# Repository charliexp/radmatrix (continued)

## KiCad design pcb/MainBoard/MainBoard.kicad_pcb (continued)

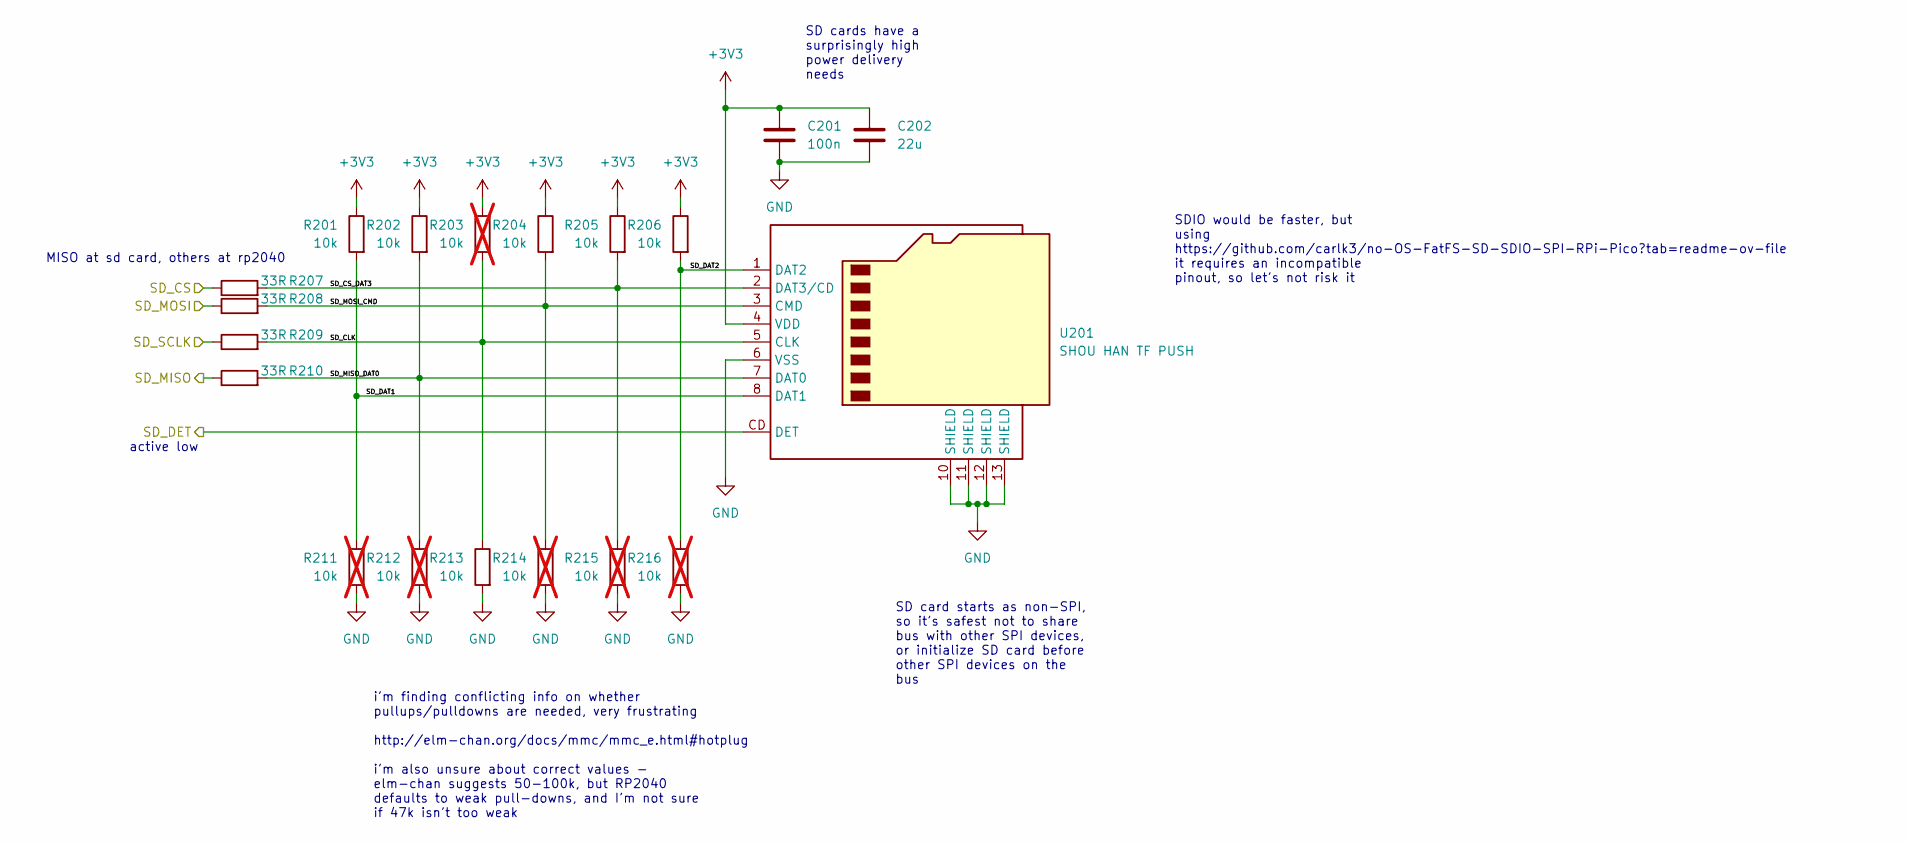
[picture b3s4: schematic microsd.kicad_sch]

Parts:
C201: 100n; C_0402_1005Metric; LCSC C1525
C202: 22u; C_0805_2012Metric; LCSC C45783
R201, R202, R204, R205, R206, R213: 10k; R_0603_1608Metric; LCSC C25804
R203, R211, R212, R214, R215, R216: 10k; R_0603_1608Metric; LCSC C25804; not fitted
R207, R208, R209, R210: 33R; R_0402_1005Metric; LCSC C25105
U201: SHOU HAN TF PUSH; micro-sd-tf-push; LCSC C393941

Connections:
+3V3: C201.1, C202.1, R201.1, R202.1, R203.1, R204.1, R205.1, R206.1, U201.4 (VDD); also elsewhere on the board
/SD_CS: R207.1; also elsewhere on the board
/SD_DET: U201.CD (DET); also elsewhere on the board
/SD_MISO: R210.1; also elsewhere on the board
/SD_MOSI: R208.1; also elsewhere on the board
/SD_SCLK: R209.1; also elsewhere on the board
/microsd/SD_CLK: R203.2, R209.2, R213.1, U201.5 (CLK)
/microsd/SD_CS_DAT3: R205.2, R207.2, R215.1, U201.2 (DAT3/CD)
/microsd/SD_DAT1: R201.2, R211.1, U201.8 (DAT1)
/microsd/SD_DAT2: R206.2, R216.1, U201.1 (DAT2)
/microsd/SD_MISO_DAT0: R202.2, R210.2, R212.1, U201.7 (DAT0)
/microsd/SD_MOSI_CMD: R204.2, R208.2, R214.1, U201.3 (CMD)
GND: C201.2, C202.2, R211.2, R212.2, R213.2, R214.2, R215.2, R216.2, U201.6 (VSS), U201.10 (SHIELD), U201.11 (SHIELD), U201.12 (SHIELD), U201.13 (SHIELD); also elsewhere on the board

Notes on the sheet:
SD card starts as non-SPI, so it's safest not to share bus with other SPI devices, or initialize SD card before other SPI devices on the bus
i'm finding conflicting info on whether pullups/pulldowns are needed, very frustrating http://elm-chan.org/docs/mmc/mmc_e.html#hotplug i'm also unsure about correct values - elm-chan suggests 50-100k, but RP2040 defaults to weak pull-downs, and I'm not sure if 47k isn't too weak
SD cards have a surprisingly high power delivery needs
SDIO would be faster, but using https://github.com/carlk3/no-OS-FatFS-SD-SDIO-SPI-RPi-Pico?tab=readme-ov-file it requires an incompatible pinout, so let's not risk it
active low
MISO at sd card, others at rp2040

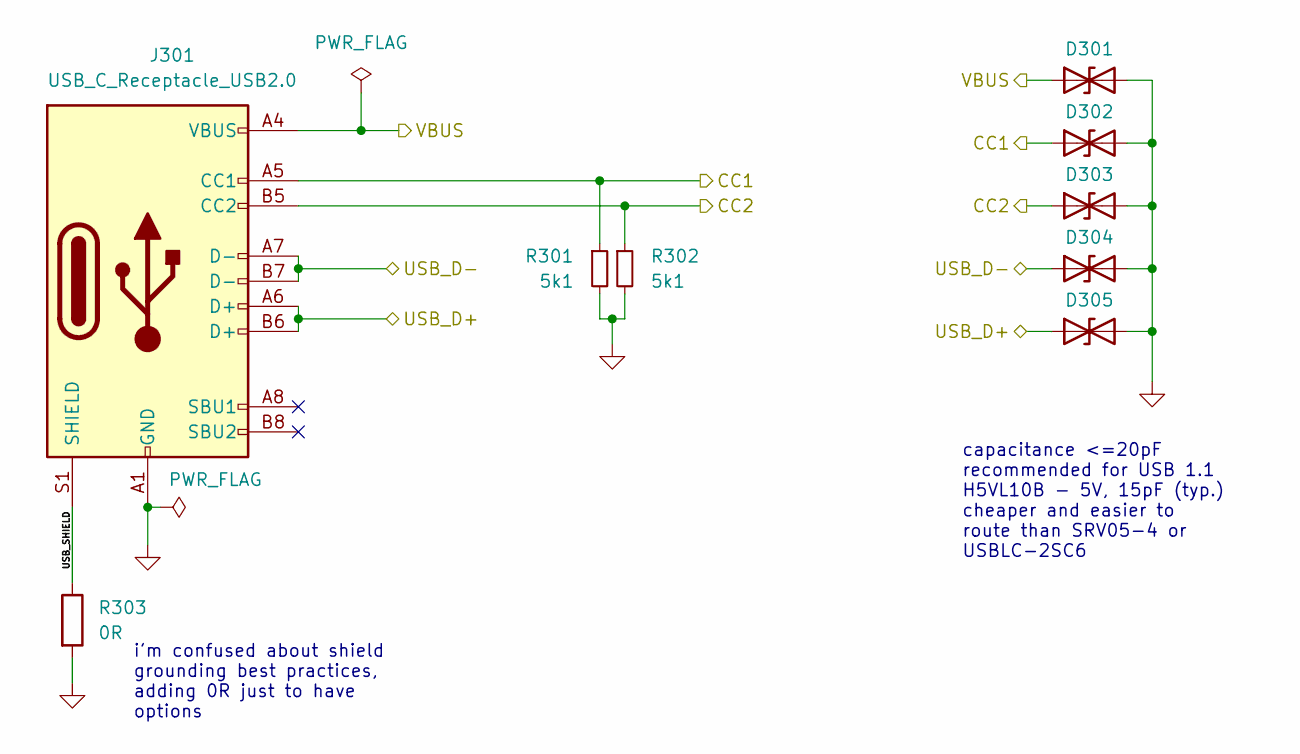
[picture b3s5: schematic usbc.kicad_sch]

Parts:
D301, D302, D303, D304, D305: H5VL10B; DFN1006_TVS; LCSC C7420372
J301: USB_C_Receptacle_USB2.0; USB_C_Receptacle_HRO_TYPE-C-31-M-12; LCSC C165948
R301, R302: 5k1; R_0402_1005Metric; LCSC C25905
R303: 0R; R_0603_1608Metric; LCSC C21189

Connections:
/CC1: D302.1 (A1), J301.A5 (CC1), R301.1; also elsewhere on the board
/CC2: D303.1 (A1), J301.B5 (CC2), R302.1; also elsewhere on the board
/USB_D+: D305.1 (A1), J301.A6 (D+), J301.B6 (D+); also elsewhere on the board
/USB_D-: D304.1 (A1), J301.A7 (D-), J301.B7 (D-); also elsewhere on the board
/power/VBUS: D301.1 (A1), J301.A4 (VBUS), J301.A9 (VBUS), J301.B4 (VBUS), J301.B9 (VBUS); also elsewhere on the board
/usbc/USB_SHIELD: J301.S1 (SHIELD), R303.1
GND: D301.2 (A2), D302.2 (A2), D303.2 (A2), D304.2 (A2), D305.2 (A2), J301.A1 (GND), J301.A12 (GND), J301.B1 (GND), J301.B12 (GND), R301.2, R302.2, R303.2; also elsewhere on the board

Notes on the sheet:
capacitance <=20pF recommended for USB 1.1 H5VL10B - 5V, 15pF (typ.) cheaper and easier to route than SRV05-4 or USBLC-2SC6
i'm confused about shield grounding best practices, adding 0R just to have options

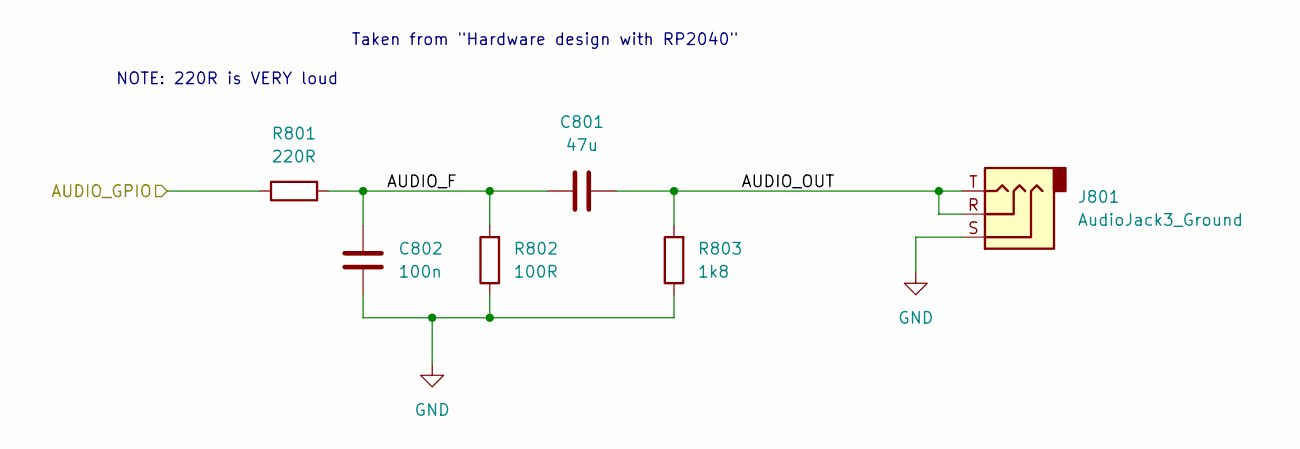
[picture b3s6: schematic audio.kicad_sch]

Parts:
C801: 47u; C_0805_2012Metric; LCSC C16780
C802: 100n; C_0402_1005Metric; LCSC C1525
J801: AudioJack3_Ground; 3.5mm-audio-jack
R801: 220R; R_0603_1608Metric; LCSC C22962
R802: 100R; R_0402_1005Metric; LCSC C25076
R803: 1k8; R_0603_1608Metric; LCSC C4177

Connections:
/AUDIO_GPIO: R801.1; also elsewhere on the board
/audio/AUDIO_F: C801.1, C802.1, R801.2, R802.2
/audio/AUDIO_OUT: C801.2, J801.R, J801.T, R803.2
GND: C802.2, J801.S, R802.1, R803.1; also elsewhere on the board

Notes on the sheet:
NOTE: 220R is VERY loud
Taken from "Hardware design with RP2040"

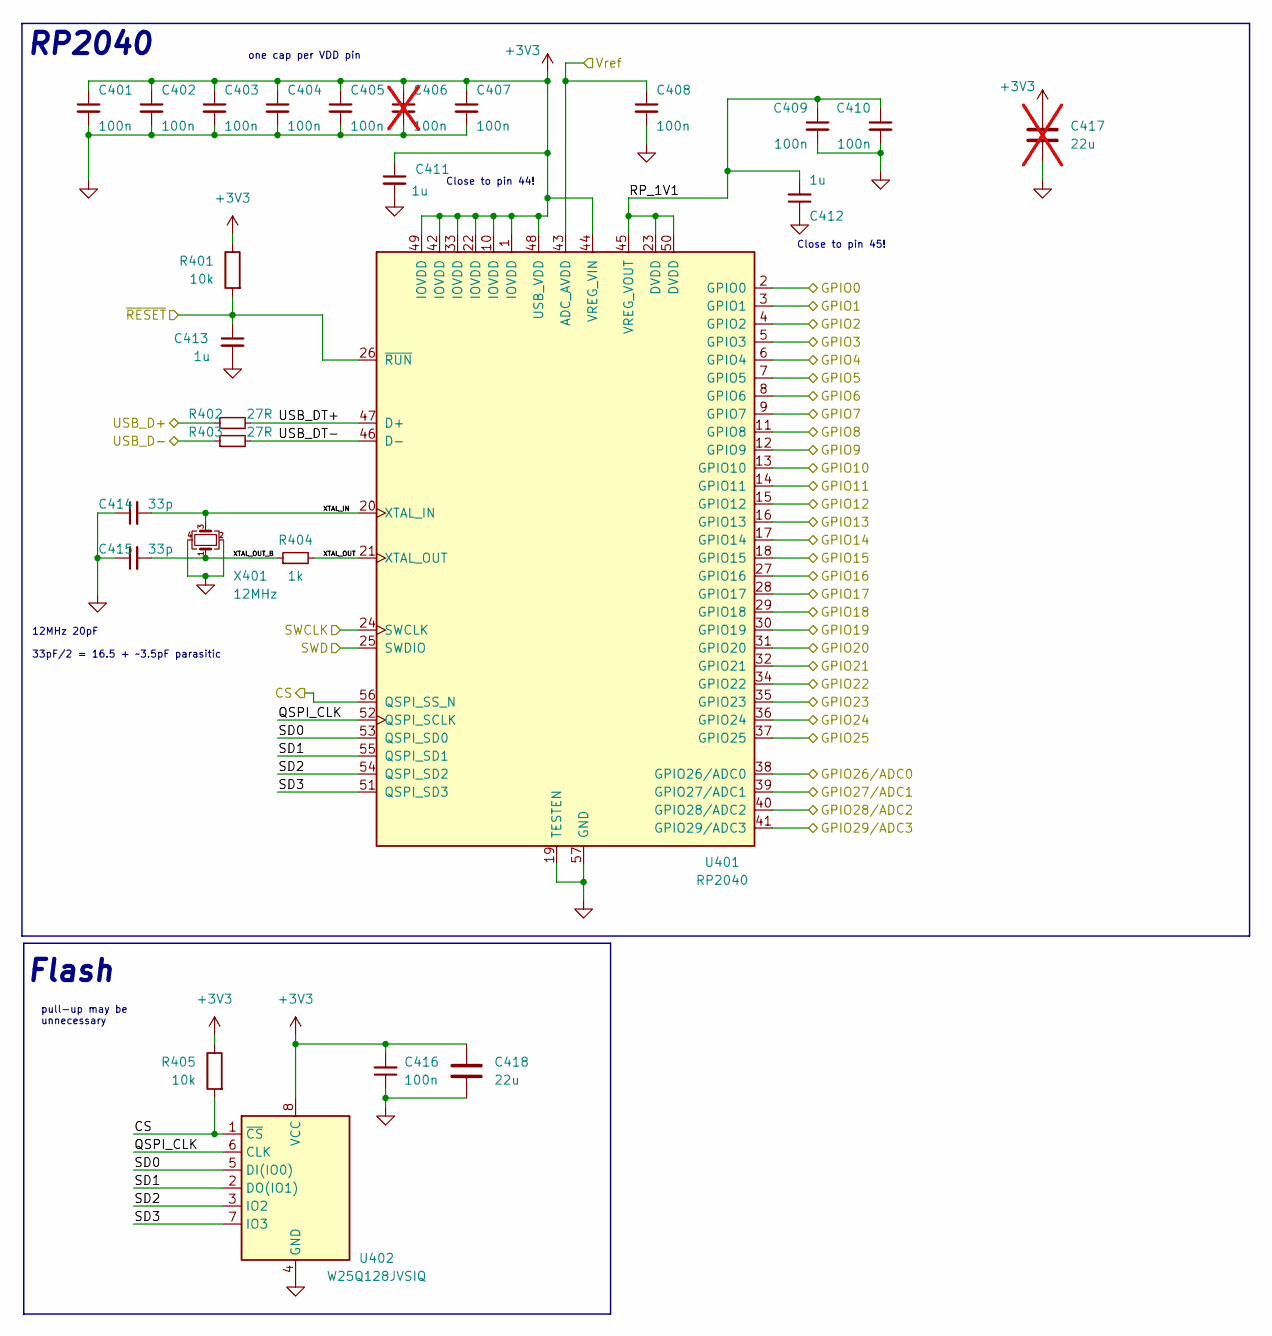
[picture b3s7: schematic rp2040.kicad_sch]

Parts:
C401, C402, C403, C404, C405, C407, C408, C409, C410, C416: 100n; C_0402_1005Metric; LCSC C1525
C406: 100n; C_0402_1005Metric; LCSC C1525; not fitted
C411, C412, C413: 1u; C_0402_1005Metric; LCSC C52923
C414, C415: 33p; C_0402_1005Metric; LCSC C1570
C417: 22u; C_0805_2012Metric; LCSC C45783; not fitted
C418: 22u; C_0805_2012Metric; LCSC C45783
R401, R405: 10k; R_0402_1005Metric; LCSC C25744
R402, R403: 27R; R_0603_1608Metric; LCSC C25190
R404: 1k; R_0402_1005Metric; LCSC C11702
U401: RP2040; RP2040-QFN-56; LCSC C2040
U402: W25Q128JVSIQ; SOIC-8_5.23x5.23mm_P1.27mm; LCSC C97521
X401: 12MHz; Crystal_SMD_3225-4Pin_3.2x2.5mm; LCSC C9002

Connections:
+3V3: C401.1, C402.1, C403.1, C404.1, C405.1, C406.1, C407.1, C411.1, C416.2, C417.1, C418.1, R401.1, R405.1, U401.1 (IOVDD), U401.10 (IOVDD), U401.22 (IOVDD), U401.33 (IOVDD), U401.42 (IOVDD), U401.44 (VREG_VIN), U401.48 (USB_VDD), U401.49 (IOVDD), U402.8 (VCC); also elsewhere on the board
/5v_sense_F: U401.40 (GPIO28/ADC2); also elsewhere on the board
/AUDIO_GPIO: U401.11 (GPIO8); also elsewhere on the board
/CAN_RXD: U401.7 (GPIO5); also elsewhere on the board
/CAN_S: U401.8 (GPIO6); also elsewhere on the board
/CAN_TXD: U401.9 (GPIO7); also elsewhere on the board
/CC1_F: U401.38 (GPIO26/ADC0); also elsewhere on the board
/CC2_F: U401.39 (GPIO27/ADC1); also elsewhere on the board
/COL_RCLK: U401.35 (GPIO23); also elsewhere on the board
/COL_SER: U401.32 (GPIO21); also elsewhere on the board
/COL_SRCLK: U401.36 (GPIO24); also elsewhere on the board
/COL_~OE: U401.34 (GPIO22); also elsewhere on the board
/COL_~SRCLR: U401.37 (GPIO25); also elsewhere on the board
/CS: R405.2, U401.56 (QSPI_SS_N), U402.1 (~CS); also elsewhere on the board
/GPIO9: U401.12 (GPIO9); also elsewhere on the board
/GPIO10: U401.13 (GPIO10); also elsewhere on the board
/GPIO11: U401.14 (GPIO11); also elsewhere on the board
/GPIO12: U401.15 (GPIO12); also elsewhere on the board
/GPIO13: U401.16 (GPIO13); also elsewhere on the board
/Isense_F: U401.41 (GPIO29/ADC3); also elsewhere on the board
/ROW_RCLK: U401.31 (GPIO20); also elsewhere on the board
/ROW_SER_J: U401.17 (GPIO14); also elsewhere on the board
/ROW_SRCLK: U401.29 (GPIO18); also elsewhere on the board
/ROW_~OE: U401.30 (GPIO19); also elsewhere on the board
/ROW_~SRCLR_J: U401.18 (GPIO15); also elsewhere on the board
/SD_CS: U401.3 (GPIO1); also elsewhere on the board
/SD_DET: U401.6 (GPIO4); also elsewhere on the board
/SD_MISO: U401.2 (GPIO0); also elsewhere on the board
/SD_MOSI: U401.5 (GPIO3); also elsewhere on the board
/SD_SCLK: U401.4 (GPIO2); also elsewhere on the board
/SWCLK: U401.24 (SWCLK); also elsewhere on the board
/SWD: U401.25 (SWDIO); also elsewhere on the board
/UART_RX: U401.28 (GPIO17); also elsewhere on the board
/UART_TX: U401.27 (GPIO16); also elsewhere on the board
/USB_D+: R402.1; also elsewhere on the board
/USB_D-: R403.1; also elsewhere on the board
/rp2040/QSPI_CLK: U401.52 (QSPI_SCLK), U402.6 (CLK)
/rp2040/RP_1V1: C409.1, C410.1, C412.2, U401.23 (DVDD), U401.45 (VREG_VOUT), U401.50 (DVDD)
/rp2040/SD0: U401.53 (QSPI_SD0), U402.5 (DI(IO0))
/rp2040/SD1: U401.55 (QSPI_SD1), U402.2 (DO(IO1))
/rp2040/SD2: U401.54 (QSPI_SD2), U402.3 (IO2)
/rp2040/SD3: U401.51 (QSPI_SD3), U402.7 (IO3)
/rp2040/USB_DT+: R402.2, U401.47 (D+)
/rp2040/USB_DT-: R403.2, U401.46 (D-)
/rp2040/XTAL_IN: C414.2, U401.20 (XTAL_IN), X401.3
/rp2040/XTAL_OUT: R404.2, U401.21 (XTAL_OUT)
/rp2040/XTAL_OUT_B: C415.2, R404.1, X401.1
/~RESET: C413.1, R401.2, U401.26 (~RUN); also elsewhere on the board
GND: C401.2, C402.2, C403.2, C404.2, C405.2, C406.2, C407.2, C408.2, C409.2, C410.2, C411.2, C412.1, C413.2, C414.1, C415.1, C416.1, C417.2, C418.2, U401.19 (TESTEN), U401.57 (GND), U402.4 (GND), X401.2, X401.4; also elsewhere on the board
Vref: C408.1, U401.43 (ADC_AVDD); also elsewhere on the board

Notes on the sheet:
pull-up may be unnecessary
Close to pin 45!
one cap per VDD pin
12MHz 20pF 33pF/2 = 16.5 + ~3.5pF parasitic
Close to pin 44!
RP2040
Flash

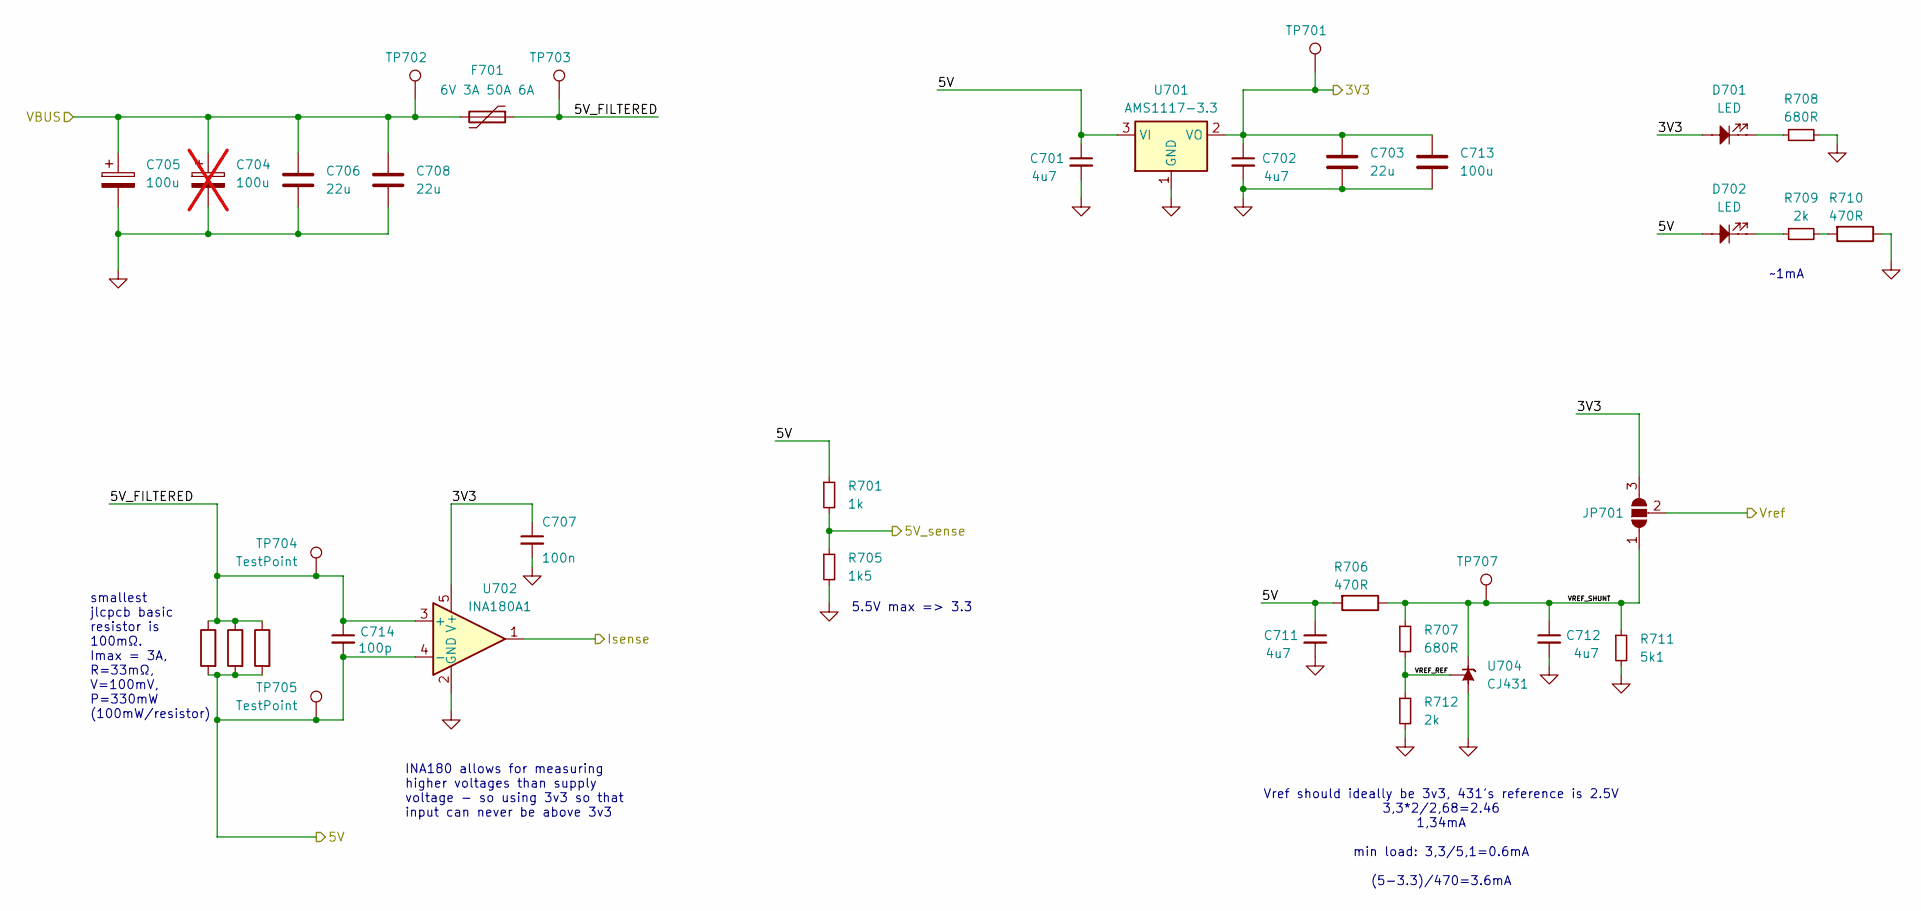
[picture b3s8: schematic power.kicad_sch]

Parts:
C701, C702, C711, C712: 4u7; C_0805_2012Metric; LCSC C1779
C703, C706, C708: 22u; C_0805_2012Metric; LCSC C45783
C704: 100u; CP_EIA-3528-15_AVX-H; LCSC C16133; not fitted
C705: 100u; CP_Elec_6.3x7.7
C707: 100n; C_0402_1005Metric; LCSC C1525
C713: 100u; C_1206_3216Metric; LCSC C15008
C714: 100p; C_0402_1005Metric; LCSC C1546
D701, D702: LED; D_0603_1608Metric; LCSC C2986059
F701: 6V 3A 50A 6A; Fuse_1210_3225Metric_Pad1.42x2.65mm_HandSolder; LCSC C2844234
JP701: SolderJumper_3_Open; SolderJumper-3_Open_RoundedPad_Smol
R701: 1k; R_0402_1005Metric; LCSC C11702
R702, R703, R704: 100mΩ; R_1206_3216Metric; LCSC C25334
R705: 1k5; R_0402_1005Metric; LCSC C25867
R706, R710: 470R; R_0603_1608Metric; LCSC C23179
R707, R708: 680R; R_0402_1005Metric; LCSC C25130
R709, R712: 2k; R_0402_1005Metric; LCSC C4109
R711: 5k1; R_0402_1005Metric; LCSC C25905
TP701, TP702, TP703, TP704, TP705, TP707: TestPoint; TestPoint_Pad_D1.0mm
U701: AMS1117-3.3; SOT-223-3_TabPin2; LCSC C6186
U702: INA180A1; SOT-23-5; LCSC C122228
U704: CJ431; SOT-23; LCSC C3113

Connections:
+3V3: C702.1, C703.1, C707.1, C713.1, D701.2, JP701.3 (B), TP701.1, U701.2 (VO), U702.5 (V+); also elsewhere on the board
+5V: C701.1, C711.1, C714.2, D702.2, R701.1, R702.2, R703.2, R704.2, R706.2, TP705.1, U701.3 (VI), U702.4 (-); also elsewhere on the board
/5V_sense: R701.2, R705.1; also elsewhere on the board
/Isense: U702.1; also elsewhere on the board
/power/5V_FILTERED: C714.1, F701.1, R702.1, R703.1, R704.1, TP703.1, TP704.1, U702.3 (+)
/power/VBUS: C704.1, C705.1, C706.1, C708.1, F701.2, TP702.1; also elsewhere on the board
/power/VREF_REF: R707.2, R712.1, U704.2 (REF)
/power/VREF_SHUNT: C712.1, JP701.1 (A), R706.1, R707.1, R711.1, TP707.1, U704.1 (K)
GND: C701.2, C702.2, C703.2, C704.2, C705.2, C706.2, C707.2, C708.2, C711.2, C712.2, C713.2, R705.2, R708.1, R710.1, R711.2, R712.2, U701.1 (GND), U702.2 (GND), U704.3 (A); also elsewhere on the board
unnamed: D701.1, R708.2
unnamed: D702.1, R709.1
unnamed: R709.2, R710.2
Vref: JP701.2 (C); also elsewhere on the board

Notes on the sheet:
smallest jlcpcb basic resistor is 100mΩ. Imax = 3A, R=33mΩ, V=100mV, P=330mW (100mW/resistor)
INA180 allows for measuring higher voltages than supply voltage - so using 3v3 so that input can never be above 3v3
~1mA
5.5V max => 3.3
Vref should ideally be 3v3, 431's reference is 2.5V 3,3*2/2,68=2.46 1,34mA min load: 3,3/5,1=0.6mA (5-3.3)/470=3.6mA

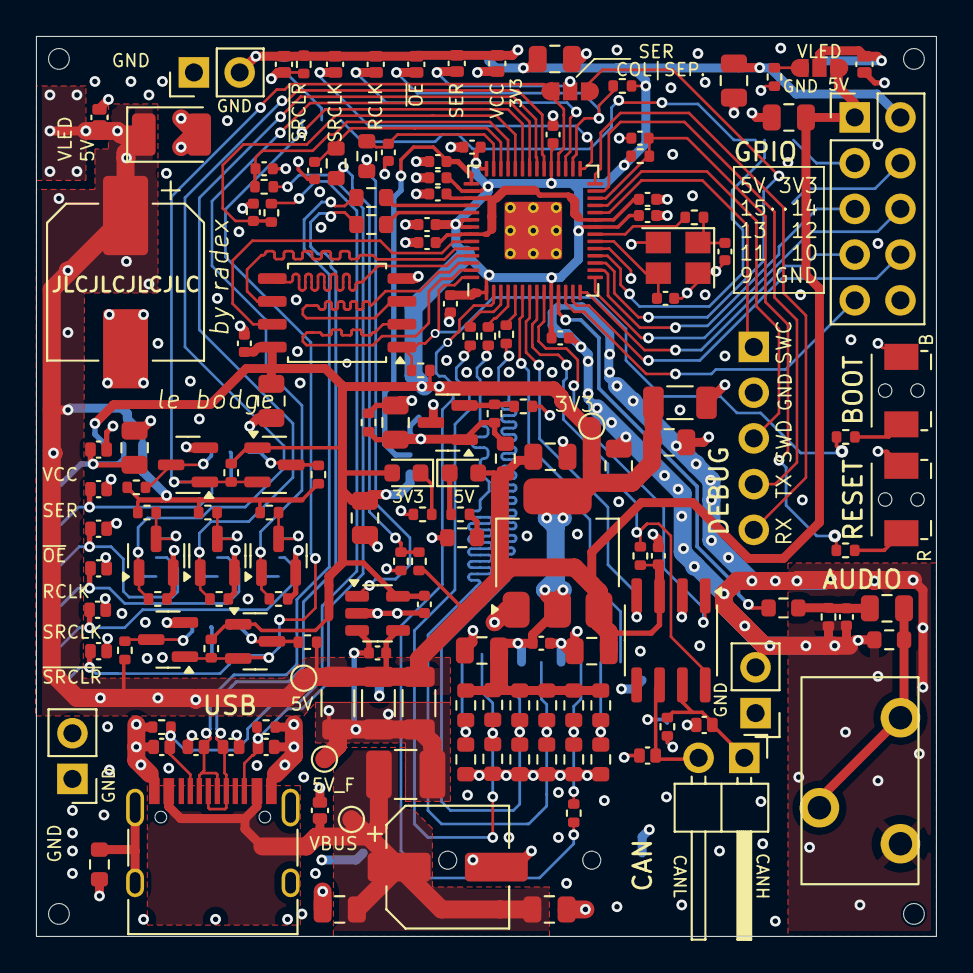
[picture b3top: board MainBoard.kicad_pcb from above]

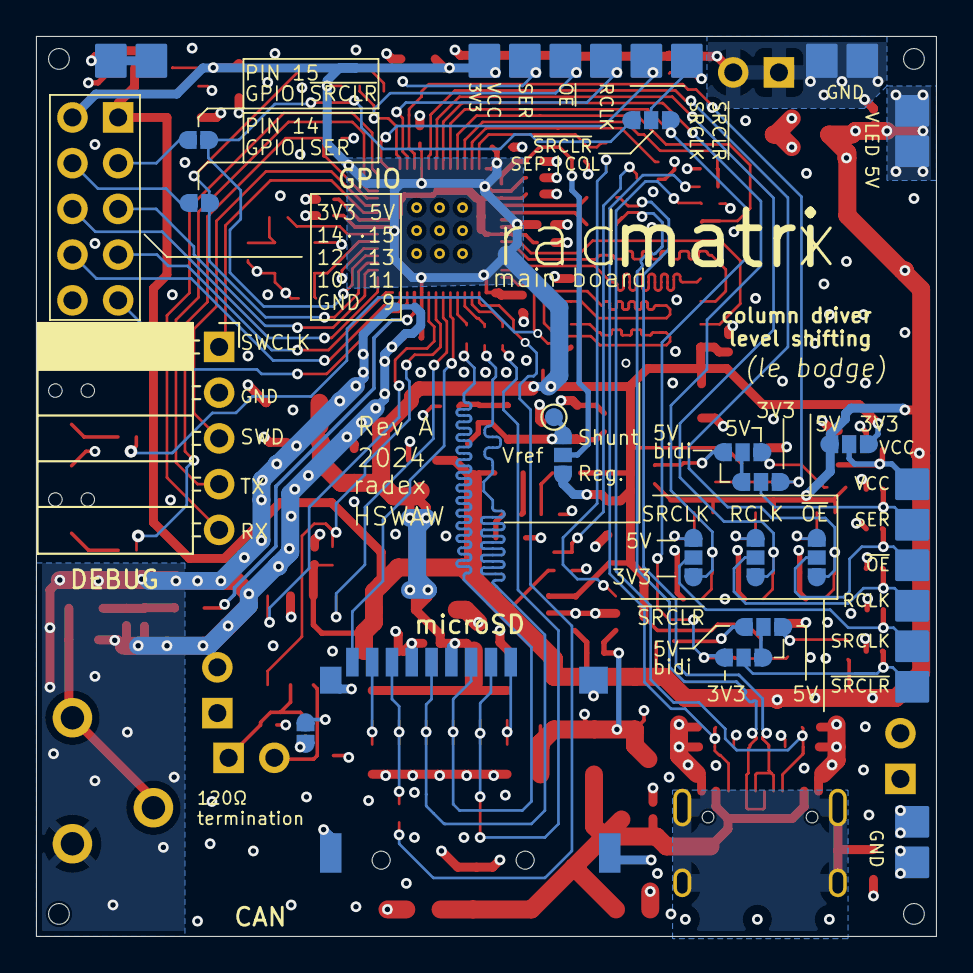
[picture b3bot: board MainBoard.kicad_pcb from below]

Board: 4 copper layers, 50.0 x 50.0 mm, 198 parts (36 on the bottom side), 97 nets.

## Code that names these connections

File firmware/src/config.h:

#pragma once

#ifndef _config_h
#define _config_h

// --- pinout ---

#define AUDIO_PIN 8

#define SD_PIN_SS 1
#define SD_PIN_SCK 2
#define SD_PIN_MOSI 3
#define SD_PIN_MISO 0
#define SD_HAS_DETECTION true
#define SD_DET_PIN 4

#define CAN_ENABLED true
#define CAN_PIN_RX 5
#define CAN_PIN_TX 7
#define CAN_PIN_SILENT 6

#define UART_TX_PIN 16
#define UART_RX_PIN 17

// NOTE: with current layout, 9-15 are free GPIOs (14, 15 only when using shared SER, SRCLR)
#define NEXT_PIN 9

#define CC1_PIN 26
#define CC2_PIN 27
#define V_SENSE_PIN 28
#define I_SENSE_PIN 29

#if CC1_PIN < 26 || CC1_PIN > 29 || \
    CC2_PIN < 26 || CC2_PIN > 29 || \
    V_SENSE_PIN < 26 || V_SENSE_PIN > 29 || \
    I_SENSE_PIN < 26 || I_SENSE_PIN > 29
#error "Invalid ADC pin"
#endif

// --- pinout - screen ---

// #define COMMON_SER 21
// #define COMMON_RCLK 23
// #define COMMON_SRCLR 25

#define COL_SER 21 // orig: 21
#define COL_OE 22 // orig: 22
#define COL_RCLK 23 // orig: 23
#define COL_SRCLK 24 // orig: 24
#define COL_SRCLR 25 // orig: 25

#define ROW_SER 14
#define ROW_OE 19
#define ROW_RCLK 20
#define ROW_SRCLK 18
#define ROW_SRCLR 15

#define COL_SER_INVERTED true
#define COL_OE_INVERTED false
#define COL_RCLK_INVERTED false
#define COL_SRCLK_INVERTED false
#define COL_SRCLR_INVERTED false

// --- screen settings ---

#define ROW_MODULES 3
#define COL_MODULES 4

#define COLOR_BITS 8

#define MAX_FPS 30
#define MAX_LENGTH_MIN 10

#define ROW_COUNT ROW_MODULES * 20
#define COL_COUNT COL_MODULES * 20

// --- audio settings ---

#define AUDIO_RATE 44000.0f
#define BUFFER_LEN 512*16

// --- other settings ---

#define CPU_CLOCK_HZ 133000000.0f
#define SD_CARD_BAUD_RATE 12 * 1000 * 1000
#define REFERENCE_VOLTAGE 3.3f // for ADC
#define CURRENT_FACTOR 1.0f // for current sensor
#define CAN_BITRATE 500000

// --- debug settings ---

#define DEBUG_TEST_FRAME false
#define DEBUG_FIRST_FRAME false
#define DEBUG_FRAMEBUFFER false

// --- screen - performance ---
// NOTE: In case of screen glitching, these may need to be tweaked to decrease
// data rate to the display and stay within the limits of the hardware/electrical connection
#define LEDS_PIO_CLKDIV 3
// Also see leds.pio where delays may be adjusted (need manual compilation)

// --- screen - color correction ---
// I do not understand color correction, gamma, it's all black magic to me
// This was manually tuned using DEBUG_TEST_FRAME=true test pattern
// See config.cpp
extern uint32_t brightnessPhaseDelays[COLOR_BITS];
extern uint8_t brightnessPhaseDithering[COLOR_BITS];
#define DITHERING_PHASES 20;

#endif

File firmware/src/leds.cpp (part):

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}

void clearShiftReg(uint8_t srclk, uint8_t srclr) {
  gpio_put(srclr, LOW);
  pulsePin(srclk);
  gpio_put(srclr, HIGH);
}

inline void outputEnable(uint8_t pin, bool enable) {
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  outputEnable(ROW_OE, false);

  // set up col pins
  pinMode(COL_SER, OUTPUT);
  pinMode(COL_OE, OUTPUT);
  outputEnable(ROW_OE, false);
  pinMode(COL_RCLK, OUTPUT);
  pinMode(COL_SRCLK, OUTPUT);
  pinMode(COL_SRCLR, OUTPUT);

  // set up row pins
  pinMode(ROW_SER, OUTPUT);
  pinMode(ROW_OE, OUTPUT);
  outputEnable(ROW_OE, false);
  pinMode(ROW_RCLK, OUTPUT);
  pinMode(ROW_SRCLK, OUTPUT);
  pinMode(ROW_SRCLR, OUTPUT);

  // set pin inversion
  #if COL_OE_INVERTED
  gpio_set_outover(COL_OE, GPIO_OVERRIDE_INVERT);
  #endif
  #if COL_SRCLR_INVERTED
  gpio_set_outover(COL_SRCLR, GPIO_OVERRIDE_INVERT);
  #endif

  // clear output
  clearShiftReg(COL_SRCLK, COL_SRCLR);
  clearShiftReg(ROW_SRCLK, ROW_SRCLR);

  pulsePin(COL_RCLK);
  pulsePin(ROW_RCLK);

  outputEnable(COL_OE, true); // this is fine, because we control OE via rows only
}
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  sm_config_set_fifo_join(&config, PIO_FIFO_JOIN_TX);

  // Set OUT (data) pin, connect to pad, set as output
  sm_config_set_out_pins(&config, COL_SER, 1);
  pio_gpio_init(pio, COL_SER);
  pio_sm_set_consecutive_pindirs(pio, sm, COL_SER, 1, true);
  #if COL_SER_INVERTED
  gpio_set_outover(COL_SER, GPIO_OVERRIDE_INVERT);
  #endif

  // Set sideset (SRCLK) pin, connect to pad, set as output
  sm_config_set_sideset_pins(&config, COL_SRCLK);
  pio_gpio_init(pio, COL_SRCLK);
  pio_sm_set_consecutive_pindirs(pio, sm, COL_SRCLK, 1, true);
  #if COL_SRCLK_INVERTED
  gpio_set_outover(COL_SRCLK, GPIO_OVERRIDE_INVERT);
  #endif
  // gpio_set_drive_strength(COL_SRCLK, GPIO_DRIVE_STRENGTH_12MA);

  // Set SET (RCLK) pin, connect to pad, set as output
  sm_config_set_set_pins(&config, COL_RCLK, 1);
  pio_gpio_init(pio, COL_RCLK);
  pio_sm_set_consecutive_pindirs(pio, sm, COL_RCLK, 1, true);
  #if COL_RCLK_INVERTED
  gpio_set_outover(COL_RCLK, GPIO_OVERRIDE_INVERT);
  #endif
  // gpio_set_drive_strength(COL_RCLK, GPIO_DRIVE_STRENGTH_12MA);

  // Load our configuration, and jump to the start of the program
  pio_sm_init(pio, sm, offset, &config);
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  sm_config_set_out_shift(&config, true, true, 32);

  // Set OUT/MOV (data) pin, connect to pad, set as output
  sm_config_set_out_pins(&config, ROW_SER, 1);
  pio_gpio_init(pio, ROW_SER);
  pio_sm_set_consecutive_pindirs(pio, sm, ROW_SER, 1, true);

  // Set sideset (SRCLK) pin, connect to pad, set as output
  sm_config_set_sideset_pins(&config, ROW_SRCLK);
  pio_gpio_init(pio, ROW_SRCLK);
  pio_sm_set_consecutive_pindirs(pio, sm, ROW_SRCLK, 1, true);

  // Set SET (RCLK) pin, connect to pad, set as output
  sm_config_set_set_pins(&config, ROW_RCLK, 1);
  pio_gpio_init(pio, ROW_RCLK);
  pio_sm_set_consecutive_pindirs(pio, sm, ROW_RCLK, 1, true);

  // Load our configuration, and jump to the start of the program
  pio_sm_init(pio, sm, offset, &config);
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  sm_config_set_out_shift(&config, true, true, 32);

  // Set sideset (OE) pin, connect to pad, set as output
  sm_config_set_sideset_pins(&config, ROW_OE);
  pio_gpio_init(pio, ROW_OE);
  pio_sm_set_consecutive_pindirs(pio, sm, ROW_OE, 1, true);

  // Load our configuration, and jump to the start of the program
  pio_sm_init(pio, sm, offset, &config);
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
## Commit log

2024-03-18 dump pcbs
2024-03-18 add readmes
2024-03-18 dump rp2040 firmware experiments
2024-03-23 noise generation experiments
2024-03-23 Revert "noise generation experiments"
    This reverts commit 85142798a8e0810115346d7bb67e7860ed56eca6.
2024-03-23 firmware: poc
2024-03-23 firmware: poc2
2024-03-23 show animation
2024-03-23 bad apple haha
2024-03-23 firmware/lib: +lodepng dump
2024-03-23 firmware: png decode demo
2024-03-23 remove gfx blobs
2024-03-23 firmware: decode png frames
2024-03-24 firmware: multicore demo
2024-03-24 firmware: flip display (not sure why it is decoded flipped)
2024-03-24 firmware: grayscale
2024-03-24 failed attempt to do multithreaded png decode
2024-03-24 Revert "failed attempt to do multithreaded png decode"
    This reverts commit 0f517d7d74ee5f2171b8f557d6fbb0bef516ed9e.
2024-03-24 framebuffer, brighter
2024-03-24 firmware: clean up
2024-03-24 pcb: add erratum
2024-03-28 update errata
2024-03-28 led characterization board test firmware
2024-03-28 Revert "led characterization board test firmware"
    This reverts commit bd8335af0600a93d4246c86012cdbb5c2faacff8.
2024-03-28 uart debug, apply more gamma, parallel processing
2024-04-06 pcb: mux design
2024-04-13 wip main board pcb
2024-04-14 pcb: update errata
2024-04-14 pcb: main board - contd
2024-04-14 firmware: make it work on the 40x40px screen
2024-04-14 firmware: improvements
2024-04-14 firmware: faster
2024-04-15 game of life proof of concept
2024-05-16 pwm audio poc
2024-05-16 sd card bullshit
2024-05-17 pcb progress
2024-05-17 better sd
2024-05-17 audio from sd
2024-05-17 gfx to blob, gfx sd reading poc
2024-05-17 reading gfx from sd card…
2024-05-17 audio and video
2024-05-17 move rendering to core1
2024-05-18 audio switch lol
2024-05-18 tweak config
2024-05-21 dump pcb
2024-05-23 MainBoard: fixes, simplify, BOM optimize, DRC fixes, ERC fixes
2024-05-24 some pcb review
2024-05-24 pio poc
2024-05-24 pio faster
2024-05-24 fixes
2024-05-24 more bits
2024-05-24 diagnostics
2024-05-25 audio AND video? no way!
2024-05-25 convert video
2024-05-25 playlist support
2024-05-25 readme
2024-05-25 auto playlist (badly)
2024-05-25 pcb: fixes, improvements
2024-05-26 pcb: add microswitches
2024-05-26 optimize leds stage
2024-05-26 documentation
2024-05-26 some microoptimizations
2024-05-26 optimize: rclk via pio
2024-05-26 optimize: use irq to signal readiness
2024-05-27 optimize: use PWM interrupt based delays for precision and pipelining
2024-05-27 wip optimize
2024-05-27 Revert "wip optimize"
    This reverts commit fa115e88cbc1ec61be11e3de2ae73b7d562d459b.
2024-05-27 Revert "optimize: use PWM interrupt based delays for precision and pipelining"
    This reverts commit 9f9d089e08edde53dbfe99617f444c4302a76aad.
2024-05-30 wip: pio-based delay
2024-05-30 clean up pio
2024-05-30 wip: pio-based row selection
2024-05-30 wip: pio-based everythin
2024-05-30 8 bits
2024-05-30 perf tweaks
2024-05-30 new readme
2024-05-31 +lib/can2040
2024-05-31 test: comment out old sd implementation
2024-06-01 switch to another arduino core?
2024-06-01 add no-OS-FatFS-SD-SDIO-SPI-RPi-Pico-main (wonderful name ain't it)
2024-06-01 huh still builds
2024-06-02 pio-based everything 8-bit color work!
2024-06-02 wip gamma correction
2024-06-02 gamma
2024-06-02 use new sd lib
2024-06-02 clean up
2024-06-03 begin MainBoard bringup
2024-06-03 some improvements...
2024-06-04 extract config.h
2024-06-05 leds: fix for new pcb (untested)
2024-06-05 can: add basic heartbeat (untested)
2024-06-08 wip integration hell
2024-06-10 integration hell
2024-06-10 pcb: KbdShield (wip)
2024-06-15 can: make it work
2024-06-15 platformio: upload/debug via picoprobe
2024-06-20 SD: try bumping to 24mhz
2024-06-20 pcb/main board: add errata
2024-06-20 add bitmap font rendering (untested)
2024-06-29 can: next song over can
2024-06-29 leds: make it work (again)
2024-06-30 platformio: upload by usb by default
2024-06-30 faaasteeeer
2024-06-30 improve gamma correction
2024-06-30 leds: evolve towards interrupt-friendly rendering
2024-06-30 leds: simplify/optimize render step
2024-06-30 reduce bleeding between lines :/
2024-10-06 unfinished power code
2024-10-06 more reliable config?
2024-10-06 remove while trues
2024-11-04 LedArrayMux Rev B
2024-11-04 LedArray Rev B
2024-12-07 fix load last playlist item
2024-12-07 fix flipped row and col
2024-12-07 increase matrix to 80x60px
2024-12-07 increase fps to 60
2024-12-07 Revert "increase fps to 60"
    This reverts commit 25572a5db91f49c48c6f9a128b5c0efd4455690e.
